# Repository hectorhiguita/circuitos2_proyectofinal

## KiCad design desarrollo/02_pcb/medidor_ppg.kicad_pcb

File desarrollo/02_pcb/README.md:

# PCB — Medidor PPG (KiCad 10)

Placa 80 × 52 mm, 2 capas, todo THT. Plano GND en las dos caras. DRC: 0 errores, 0 pendientes, esquema = placa.

## Archivos
| Archivo | Qué es |
|---|---|
| `medidor_ppg.kicad_pro` | Abrir en KiCad |
| `fab/medidor_ppg_gerbers_JLCPCB.zip` | Subir a JLCPCB tal cual |
| `fab/medidor_ppg_BOM.csv` | Lista de piezas de la placa |
| `fab/medidor_ppg_esquema.pdf` | Esquema para el informe |
| `fab/medidor_ppg_montaje_superior.pdf` | Guía de montaje (cara superior) |
| `img/*.png` | Vistas 3D |
| `componentes.py` | Netlist (fuente única) |
| `generar_esquema.py`, `generar_pcb.py`, `fabricar.sh` | Regeneran todo |

Regenerar: `python3 generar_esquema.py && python3 generar_pcb.py && ./fabricar.sh`.
**Riesgo:** `generar_pcb.py` sobrescribe la placa. Si la editas a mano en KiCad, no lo vuelvas a correr.

## Esquema legible por bloques
El esquema `medidor_ppg.kicad_sch` está dibujado **por etapas** (cada una en su recuadro), con la señal fluyendo de izquierda a derecha: sensor → acople → buffer → preamp → Sallen-Key → salida → protección → ADC. Lo genera `construir_esquema.py` (usa `esq_bloques_lib.py`), leyendo el mismo `componentes.py`, así que el **netlist es idéntico** al generador antiguo: la PCB, el ERC y la simulación no cambian.

- Regenerar el esquema legible: `python3 construir_esquema.py`
- Vista previa: `img/esquema_bloques.png`
- El generador antiguo por etiquetas quedó como respaldo en `generar_esquema_etiquetas.py.bak` y el esquema anterior en `medidor_ppg.kicad_sch.bak_etiquetas`.

## Opción sin PCB: baquela perforada 9 × 7 cm
Todas las huellas usan paso de 2.54 mm. Por eso la misma ubicación sirve en baquela universal (35 × 27 agujeros). Ocupa 32 × 19 agujeros.

| Archivo | Uso |
|---|---|
| `perforada/vista_componentes.pdf` | Imprimir al **100 %**, pegar sobre la baquela y pinchar las piezas |
| `perforada/vista_soldadura.pdf` | Vista desde abajo (espejada). Cada línea = un cable |
| `perforada/conexiones.md` | 99 conexiones con casilla para marcar. Ej.: `R15.1 (R5) → C12.1 (P19)` |

Columnas = letras, filas = números (como un tablero de ajedrez). Usa cable de wire-wrap o hilos de UTP. GND, +5V y +3V3 con cable más grueso.
Regenerar: `python3 perforada.py`.

## Pedido en JLCPCB
2 capas, 80×52 mm, 1.6 mm, HASL, cualquier color. 5 placas cuestan ~2 USD más el envío.

## Antes de soldar: verifica con el calibrador
1. **SuperMini:** filas a **15.24 mm**. Pon la placa sobre la serigrafía. El pin `5V` debe quedar del lado del USB, en la fila de arriba.
   Si los pines quedan al revés, se puede montar el SuperMini boca abajo: así se cruzan las filas y el orden se mantiene.
2. **Buzzer:** la pata `+` va en el pad cuadrado.

## Orden de soldadura (de bajo a alto)
1. Resistencias (paradas) y diodos. `K` en la serigrafía = cátodo (raya).
2. Zócalo DIP-14 (muesca hacia arriba en la serigrafía). El LM324 va al final.
3. Condensadores cerámicos, puntos de prueba TP1–TP7.
4. Transistor 2N3904 (cara plana como la serigrafía), trimmer RV1.
5. Condensadores de film, electrolíticos (pata larga `+`), conectores, zócalos del SuperMini y buzzer.

## Conector de energía J5 (cables al piso de la caja)
| Pin | Va a |
|---|---|
| 1 B+ | TP4056 OUT+ |
| 2 SWa | Interruptor, pata 1 |
| 3 SWb | Interruptor, pata común |
| 4 MT+ | MT3608 IN+ |
| 5 B− | TP4056 OUT− |
| 6 MT− | MT3608 IN− |
| 7 5V | MT3608 OUT+ |
| 8 G | MT3608 OUT− |

La batería va a B+ / B− del **TP4056**, no a la placa.

## Sensor J1 (JST-XH 4, hacia la pinza)
| Pin | Va a |
|---|---|
| 1 LED+ | Ánodo del LED IR (pata larga) |
| 2 LED− | Cátodo del LED IR |
| 3 PD-K | Cátodo del fotodiodo (pata corta / lado plano) |
| 4 PD-A | Ánodo del fotodiodo |

Usa cable apantallado o trenzado. La malla va a GND.

## Prueba por etapas (lo pide la guía)
1. **Sin LM324 ni SuperMini:** conecta la LiPo y ajusta el MT3608 a **5.00 V** en el pin 7 de J5.
2. Pon el SuperMini sin el LM324. Mide **3.3 V** en el pin 3V3 y **1.32 V** en TP6.
3. Pon el LM324, con el dedo en la pinza. Mira cada punto con el osciloscopio:

| TP | Etapa | Esperado |
|---|---|---|
| TP1 | Sensor | DC 0.1–1 V, pulso de pocos mV |
| TP2 | Buffer | ≈1.32 V con el pulso encima |
| TP3 | Preamp ×34 | ≈1.32 V, pulso ≈0.1 Vpp |
| TP4 | Sallen-Key | Igual, más suave |
| TP5 | **Punto 6** | 1.32 V ± 0.5 V. Nunca < 0 V ni > 2.5 V |
| TP7 | GND | Tierra del osciloscopio |

4. Ajusta RV1 hasta ver **0.8–1.6 Vpp** en TP5.

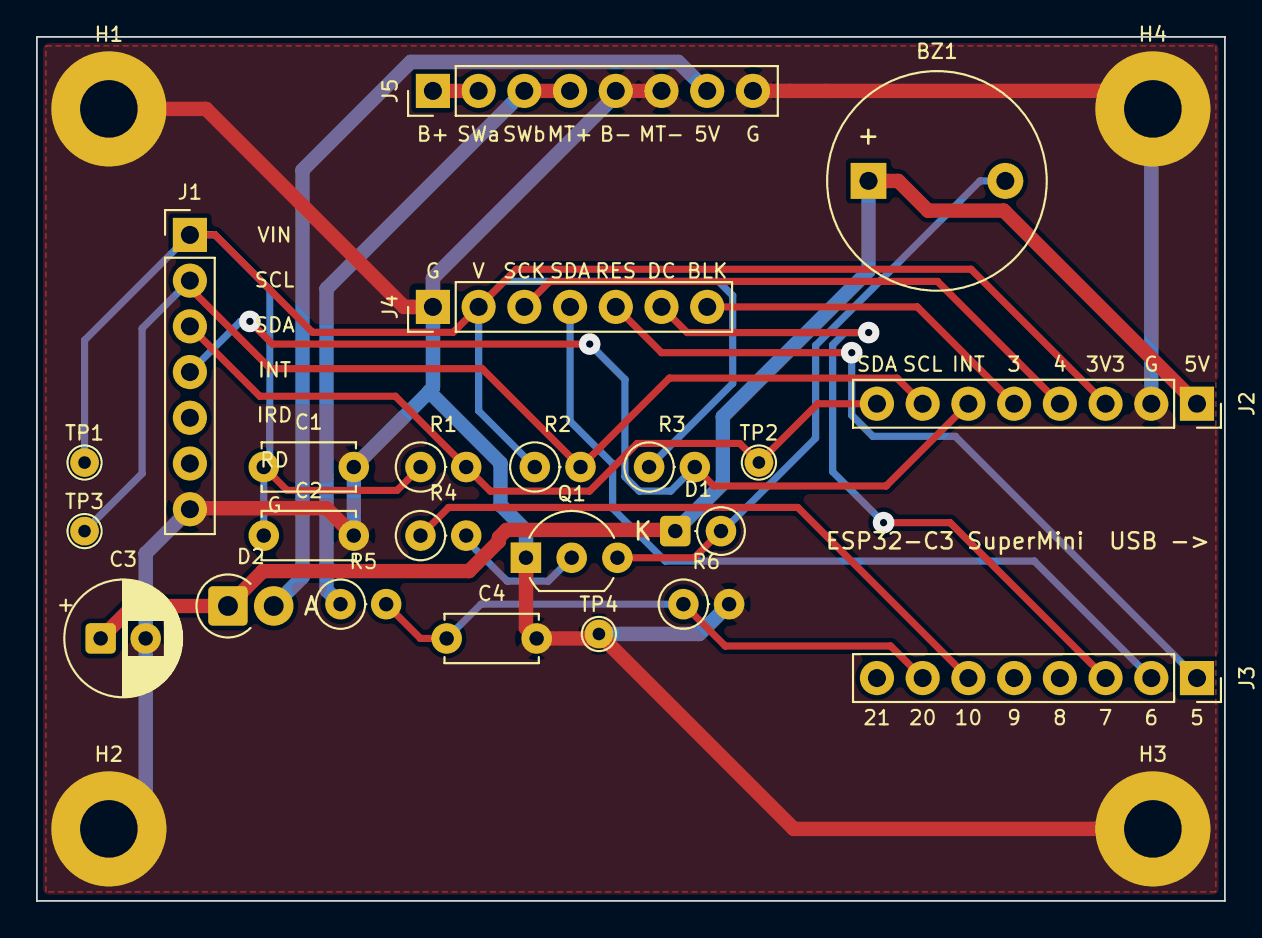
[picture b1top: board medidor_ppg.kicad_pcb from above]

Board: 2 copper layers, 66.0 x 48.0 mm, 27 parts (0 on the bottom side), 18 nets.

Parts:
BZ1: Buzzer 5V; Buzzer_12x9.5RM7.6
C1, C2, C4: 100nF; C_Disc_D5.0mm_W2.5mm_P5.00mm
C3: 100uF; CP_Radial_D6.3mm_P2.50mm
D1: 1N4148; D_DO-35_SOD27_P2.54mm_Vertical_CathodeUp
D2: 1N5819; D_DO-41_SOD81_P2.54mm_Vertical_AnodeUp
H1, H2, H3, H4: M3; MountingHole_3.2mm_M3_Pad
J1: MAX30102; PinHeader_1x07_P2.54mm_Vertical
J2: C3_5V-IO0; PinSocket_1x08_P2.54mm_Vertical
J3: C3_IO5-IO21; PinSocket_1x08_P2.54mm_Vertical
J4: TFT 1.3 ST7789; PinHeader_1x07_P2.54mm_Vertical
J5: ENERGIA; PinHeader_1x08_P2.54mm_Vertical
Q1: 2N3904; TO-92_Inline_Wide
R1, R2, R3: 4.7k; R_Axial_DIN0207_L6.3mm_D2.5mm_P2.54mm_Vertical
R4: 1k; R_Axial_DIN0207_L6.3mm_D2.5mm_P2.54mm_Vertical
R5, R6: 100k; R_Axial_DIN0207_L6.3mm_D2.5mm_P2.54mm_Vertical
TP1: +3V3; TestPoint_THTPad_D1.5mm_Drill0.7mm
TP2: SDA; TestPoint_THTPad_D1.5mm_Drill0.7mm
TP3: SCL; TestPoint_THTPad_D1.5mm_Drill0.7mm
TP4: GND; TestPoint_THTPad_D1.5mm_Drill0.7mm

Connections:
+3V3: C1.1, C2.1, J1.1, J2.3, J4.2, R1.1, R2.1, R3.1, TP1.1
+5V: BZ1.1, C3.1, D1.1, D2.1, J2.1
/+5V_B: D2.2, J5.7
/BAT: J5.1, J5.2
/BUZ: J3.6, R4.1
/BZK: BZ1.2, D1.2, Q1.3
/INT: J1.4, J2.6, R3.2
/QB: Q1.2, R4.2
/SCL: J1.2, J2.7, R2.2, TP3.1
/SDA: J1.3, J2.8, R1.2, TP2.1
/TFT_BLK: J2.5, J4.7
/TFT_DC: J3.3, J4.6
/TFT_RES: J3.1, J4.5
/TFT_SCK: J2.4, J4.3
/TFT_SDA: J3.2, J4.4
/VBAT_S: C4.1, J3.7, R5.2, R6.1
/VSW: J5.3, J5.4, R5.1
GND: C1.2, C2.2, C3.2, C4.2, H1.1, H2.1, H3.1, H4.1, J1.7, J2.2, J4.1, J5.5, J5.6, J5.8, Q1.1, R6.2, TP4.1

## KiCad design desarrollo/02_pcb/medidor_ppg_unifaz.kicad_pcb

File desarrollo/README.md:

# Medidor de ritmo cardiaco PPG — Proyecto final Circuitos Eléctricos II (ITM)

LED IR + fotodiodo → LM324 (6 etapas) → ESP32-C3 SuperMini → OLED + buzzer → MQTT → tablero + alertas por correo y WhatsApp.

| Carpeta | Contenido | Estado |
|---|---|---|
| `SPEC.md` | Especificación: pines, valores, contrato MQTT | ✅ |
| `01_analogico/` | Netlist ngspice, simulación, gráficas | ✅ simulado |
| `02_pcb/` | KiCad 10: esquema, PCB, Gerbers JLCPCB, BOM | ✅ DRC 0 errores |
| `03_firmware/` | PlatformIO (ESP32-C3) | ✅ compila, 13 pruebas OK |
| `04_iot/` | Mosquitto + Node-RED (tablero, alertas) + simulador | ✅ probado con simulador |
| `05_carcasa/` | OpenSCAD + STL | ✅ STL listos |
| `06_informe/` | Informe escrito | ✅ borrador (faltan fotos y medidas reales) |

## Lista de compras
| # | Pieza | Cant | Nota |
|---|---|---|---|
| 1 | ESP32-C3 SuperMini | 1 | USB-C |
| 2 | OLED 0.96" I2C SSD1306 (4 pines) | 1 | dirección 0x3C |
| 3 | LM324N (DIP-14) + zócalo DIP-14 | 1 | |
| 4 | LED IR 940 nm 5 mm | 1 | |
| 5 | Fotodiodo IR 5 mm (o BPW34) | 1 | **no** fototransistor |
| 6 | Batería LiPo BL-3.7V-1000-25C (68×34×6 mm) | 1 | cortar el conector rojo y soldar al TP4056 |
| 7 | Módulo TP4056 USB-C con protección (DW01) | 1 | |
| 8 | Módulo elevador MT3608 | 1 | ajustar a 5.0 V |
| 9 | Interruptor deslizante SS12D00 | 1 | |
| 10 | Buzzer activo 5 V, 12 mm | 1 | |
| 11 | Trimmer multivuelta 3296W 200 kΩ | 1 | |
| 12 | Condensador film (MKT) 1 µF 63 V | 3 | paso 5 mm |
| 13 | Condensador film 470 nF 63 V | 1 | paso 5 mm |
| 14 | Electrolítico 100 µF 16 V (6.3 mm) | 3 | |
| 15 | Cerámico 100 nF | 6 | |
| 16 | Cerámico 47 nF | 1 | |
| 17 | Cerámico 10 nF | 1 | |
| 18 | Resistencias 1/4 W: 220, 1k ×3, 1.5k ×2, 4.7k, 10k ×3, 47k ×3, 100k ×2, 330k, 470k ×2 | 19 | |
| 19 | Diodo BAT85 | 2 | Schottky |
| 20 | Diodo 1N5819 | 1 | |
| 21 | Diodo 1N4148 | 1 | |
| 22 | Transistor 2N3904 | 1 | |
| 23 | Conector JST-XH 4 pines (macho PCB + hembra con cable) | 1 | sensor |
| 24 | Regleta hembra 1×8 (2.54) | 2 | zócalo SuperMini |
| 25 | Regleta macho 1×8 y 1×4 | 1+1 | J5, J4 |
| 26 | Tornillos M3 + insertos, M2, liga | — | ver `05_carcasa/README.md` |
| 27 | PCB JLCPCB 80×52 mm | 5 | `02_pcb/fab/medidor_ppg_gerbers_JLCPCB.zip` |

## Orden sugerido
1. Pedir la PCB e imprimir la carcasa (tardan más).
2. Probar firmware y tablero **sin** hardware: `03_firmware` entorno `c3_demo` + `04_iot` con simulador.
3. Soldar y validar por etapas con el osciloscopio (`02_pcb/README.md`).
4. Ajustar RV1. Probar alertas. Tomar fotos y capturas para el informe.

## Riesgos
- **Punto 6** nunca debe pasar de 2.5 V ni bajar de 0 V. Mídelo antes de poner el SuperMini.
- Ajusta el **MT3608 a 5.0 V** antes de conectar la placa.
- La LiPo debe tener protección. No la cargues sin vigilar.
- El `.env` de `04_iot` tiene claves. No lo subas a internet.

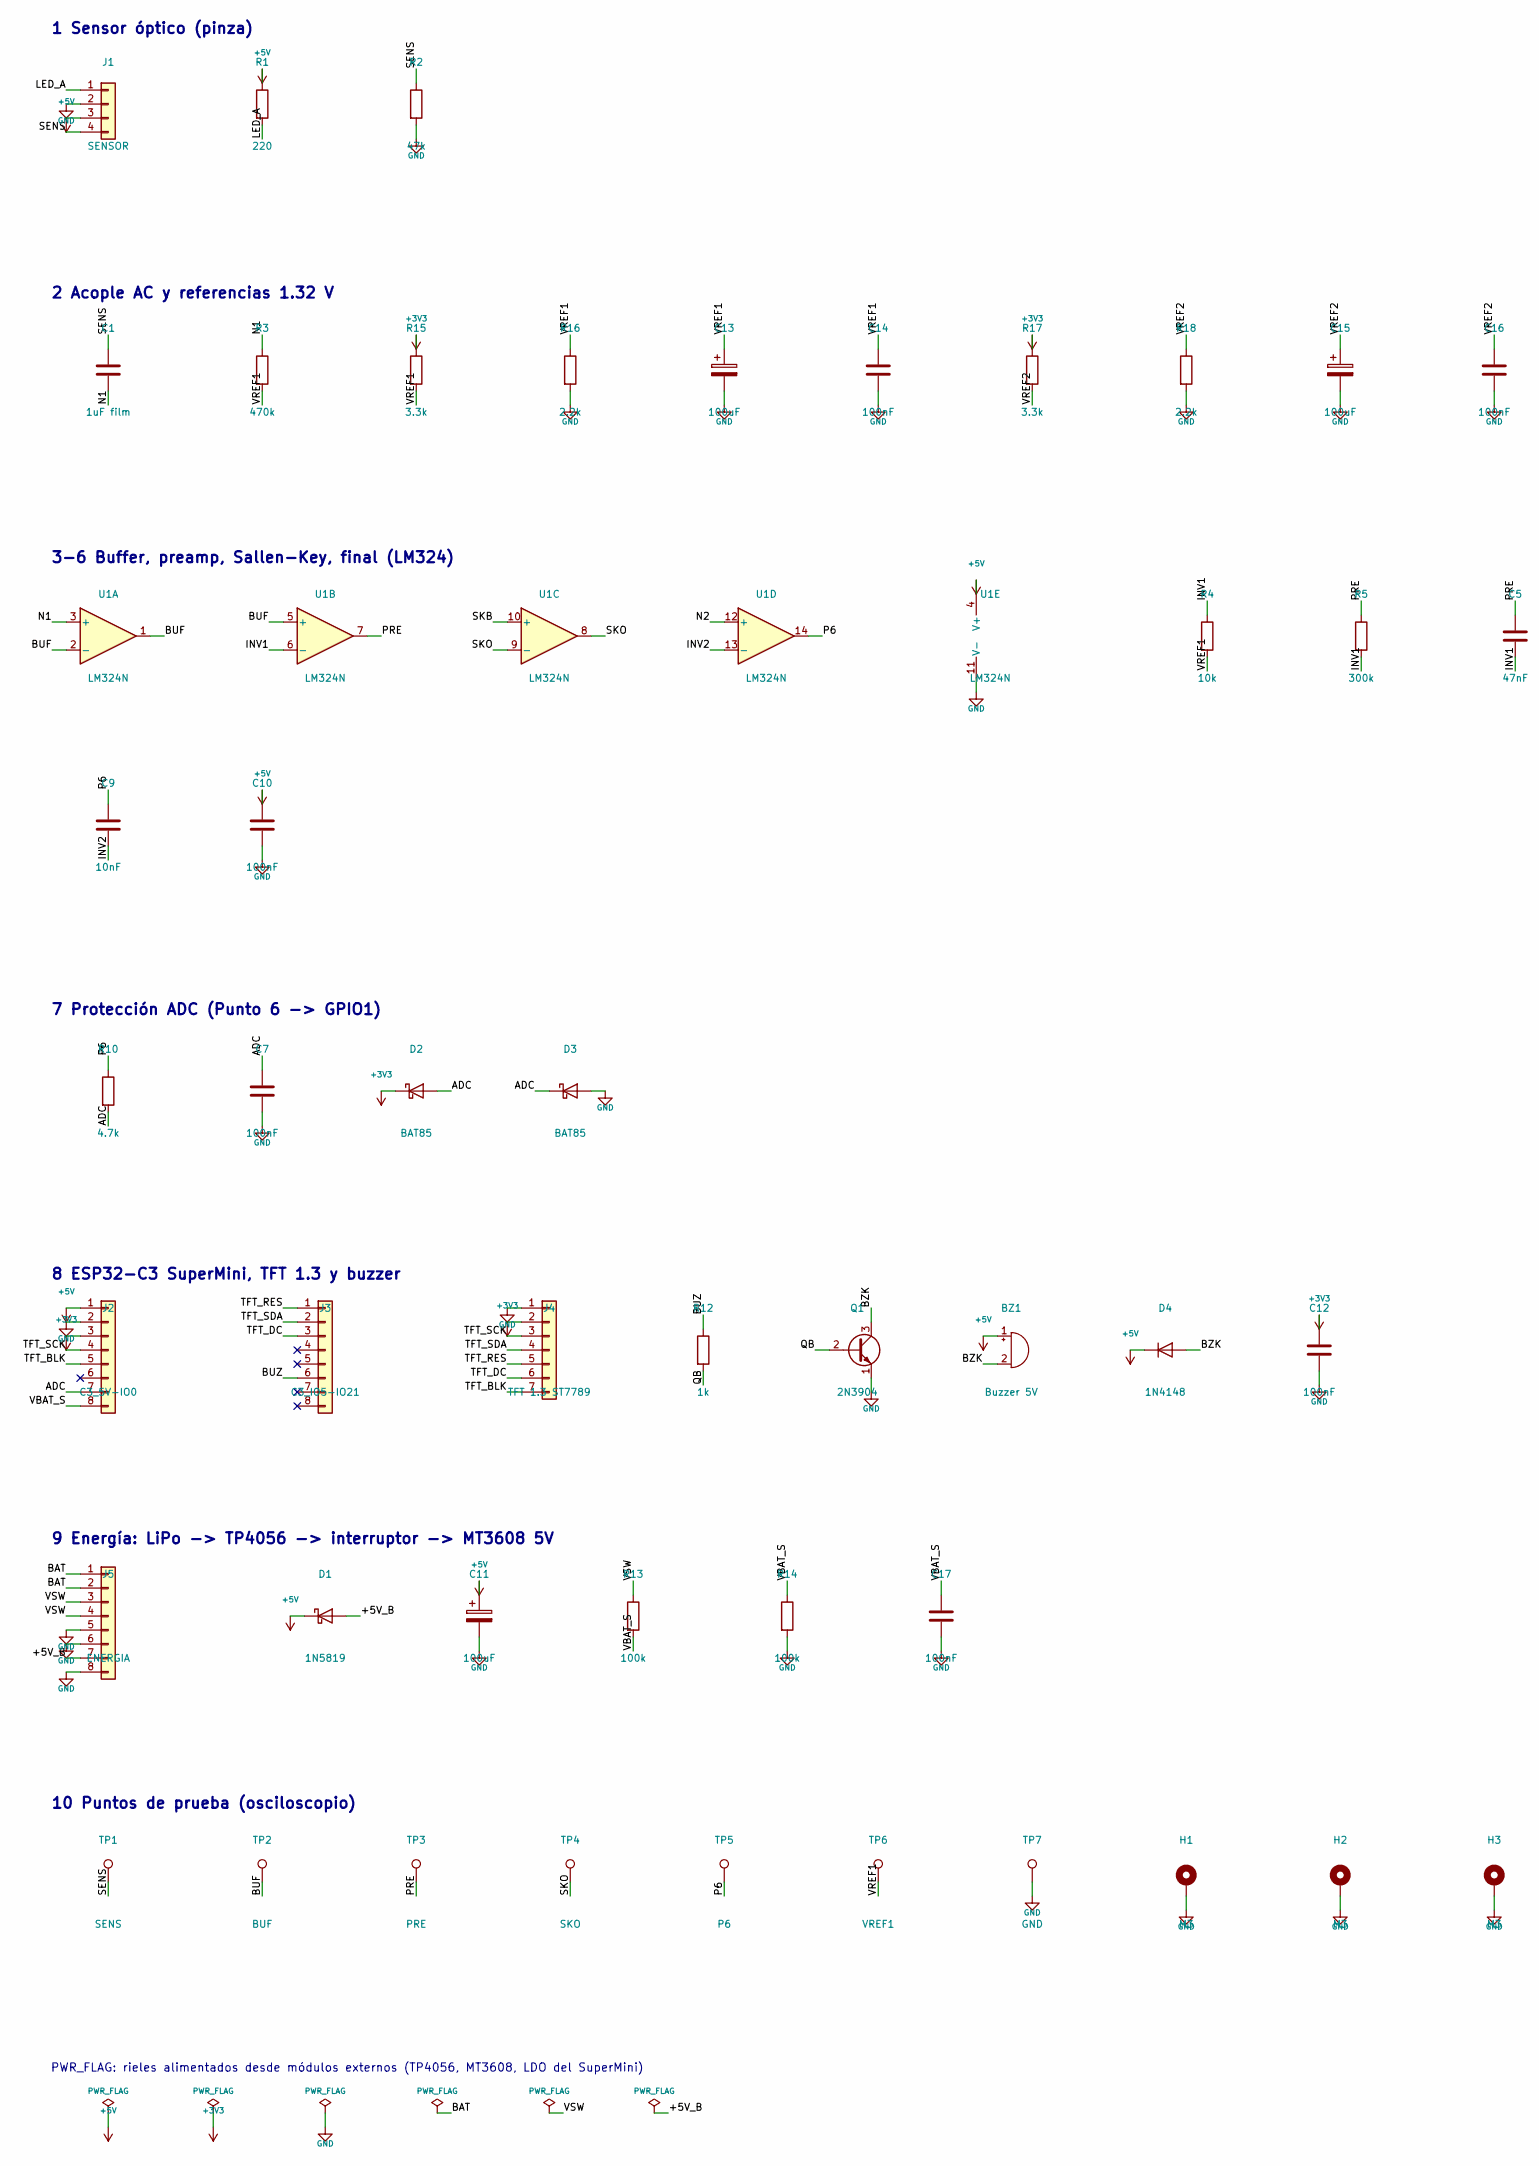
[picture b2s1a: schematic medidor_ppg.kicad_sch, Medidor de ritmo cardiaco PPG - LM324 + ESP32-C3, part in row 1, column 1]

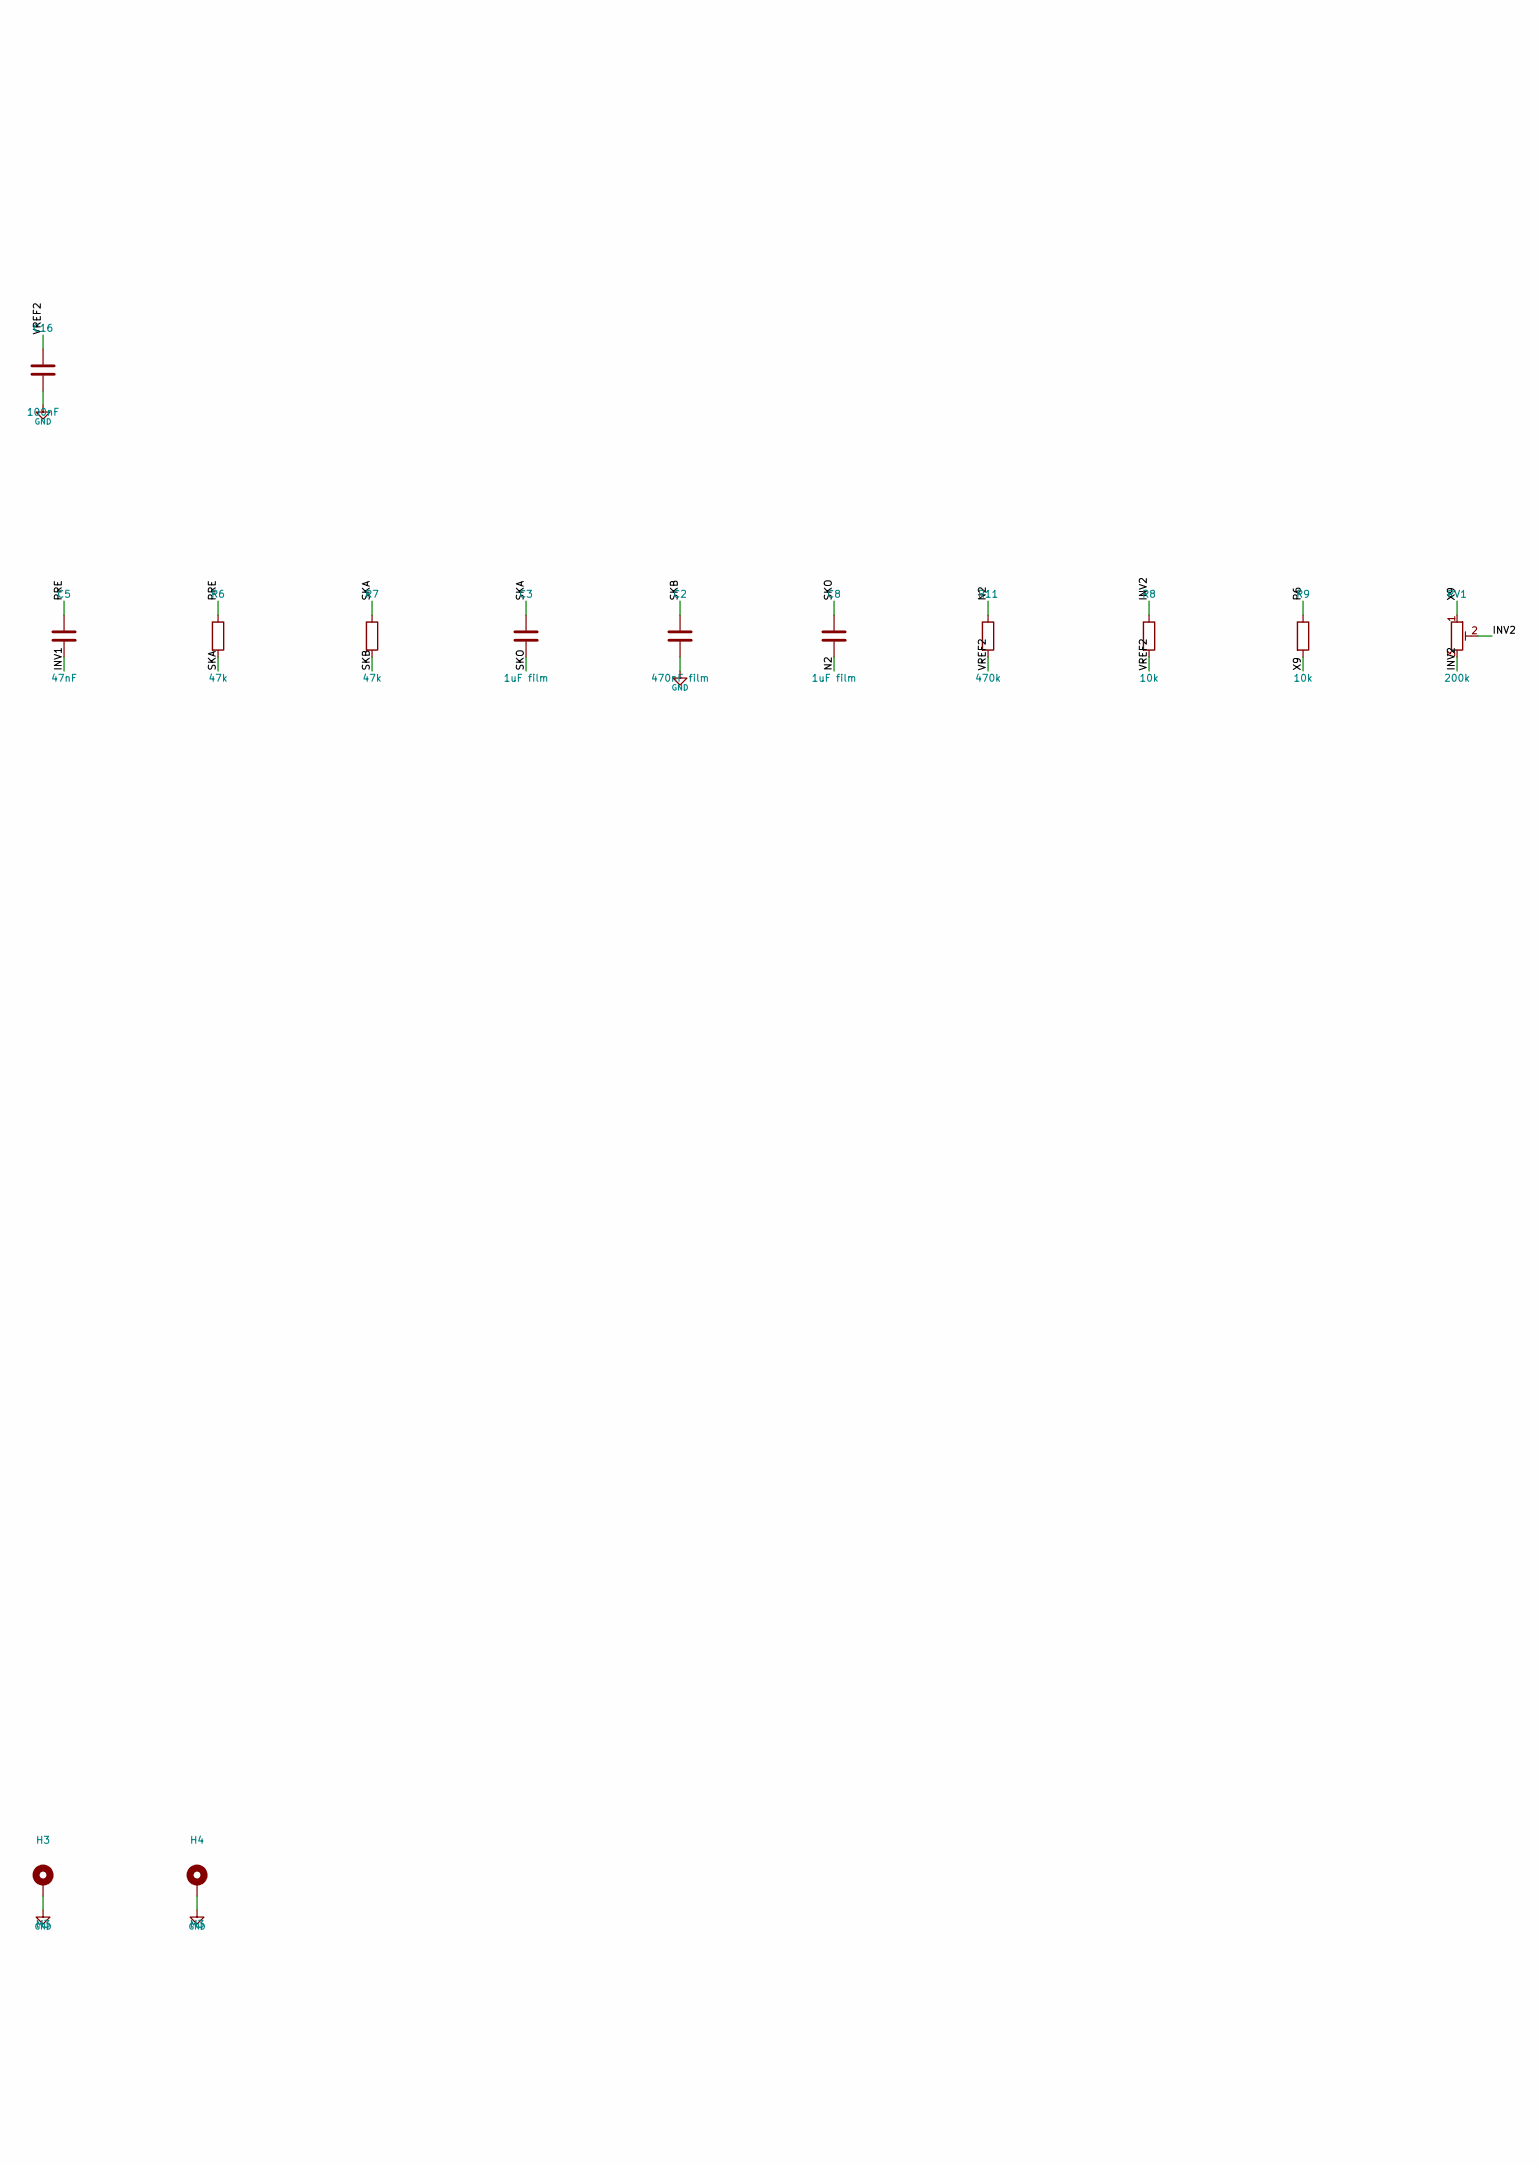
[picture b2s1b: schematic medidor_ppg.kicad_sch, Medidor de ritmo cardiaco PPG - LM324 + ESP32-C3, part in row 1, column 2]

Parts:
BZ1: Buzzer 5V; Buzzer_12x9.5RM7.6
C1, C3, C8: 1uF film; C_Rect_L7.2mm_W5.5mm_P5.00mm_FKS2_FKP2_MKS2_MKP2
C2: 470nF film; C_Rect_L7.2mm_W5.5mm_P5.00mm_FKS2_FKP2_MKS2_MKP2
C5: 47nF; C_Disc_D5.0mm_W2.5mm_P5.00mm
C7, C10, C12, C14, C16, C17: 100nF; C_Disc_D5.0mm_W2.5mm_P5.00mm
C9: 10nF; C_Disc_D5.0mm_W2.5mm_P5.00mm
C11, C13, C15: 100uF; CP_Radial_D6.3mm_P2.50mm
D1: 1N5819; D_DO-41_SOD81_P2.54mm_Vertical_AnodeUp
D2, D3: BAT85; D_DO-35_SOD27_P2.54mm_Vertical_CathodeUp
D4: 1N4148; D_DO-35_SOD27_P2.54mm_Vertical_CathodeUp
H1, H2, H3, H4: M3; MountingHole_3.2mm_M3_Pad
J1: SENSOR; JST_XH_B4B-XH-A_1x04_P2.50mm_Vertical
J2: C3_5V-IO0; PinSocket_1x08_P2.54mm_Vertical
J3: C3_IO5-IO21; PinSocket_1x08_P2.54mm_Vertical
J4: TFT 1.3 ST7789; PinHeader_1x07_P2.54mm_Vertical
J5: ENERGIA; PinHeader_1x08_P2.54mm_Vertical
Q1: 2N3904; TO-92_Inline_Wide
R1: 220; R_Axial_DIN0207_L6.3mm_D2.5mm_P2.54mm_Vertical
R2, R6, R7: 47k; R_Axial_DIN0207_L6.3mm_D2.5mm_P2.54mm_Vertical
R3, R11: 470k; R_Axial_DIN0207_L6.3mm_D2.5mm_P2.54mm_Vertical
R4, R8, R9: 10k; R_Axial_DIN0207_L6.3mm_D2.5mm_P2.54mm_Vertical
R5: 300k; R_Axial_DIN0207_L6.3mm_D2.5mm_P2.54mm_Vertical
R10: 4.7k; R_Axial_DIN0207_L6.3mm_D2.5mm_P2.54mm_Vertical
R12: 1k; R_Axial_DIN0207_L6.3mm_D2.5mm_P2.54mm_Vertical
R13, R14: 100k; R_Axial_DIN0207_L6.3mm_D2.5mm_P2.54mm_Vertical
R15, R17: 3.3k; R_Axial_DIN0207_L6.3mm_D2.5mm_P2.54mm_Vertical
R16, R18: 2.2k; R_Axial_DIN0207_L6.3mm_D2.5mm_P2.54mm_Vertical
RV1: 200k; Potentiometer_Bourns_3296W_Vertical
TP1: SENS; TestPoint_THTPad_D1.5mm_Drill0.7mm
TP2: BUF; TestPoint_THTPad_D1.5mm_Drill0.7mm
TP3: PRE; TestPoint_THTPad_D1.5mm_Drill0.7mm
TP4: SKO; TestPoint_THTPad_D1.5mm_Drill0.7mm
TP5: P6; TestPoint_THTPad_D1.5mm_Drill0.7mm
TP6: VREF1; TestPoint_THTPad_D1.5mm_Drill0.7mm
TP7: GND; TestPoint_THTPad_D1.5mm_Drill0.7mm
U1: LM324N; DIP-14_W7.62mm_Socket

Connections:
+3V3: C12.1, D2.1 (K), J2.3, J4.2, R15.1, R17.1
+5V: BZ1.1 (+), C10.1, C11.1, D1.1 (K), D4.1 (K), J1.3, J2.1, R1.1, U1.4 (V+)
/+5V_B: D1.2 (A), J5.7
/ADC: C7.1, D2.2 (A), D3.1 (K), J2.7, R10.2
/BAT: J5.1, J5.2
/BUF: TP2.1, U1.1, U1.2 (-), U1.5 (+)
/BUZ: J3.6, R12.1
/BZK: BZ1.2 (-), D4.2 (A), Q1.3 (C)
/INV1: C5.2, R4.1, R5.2, U1.6 (-)
/INV2: C9.2, R8.1, RV1.2, RV1.3, U1.13 (-)
/LED_A: J1.1, R1.2
/N1: C1.2, R3.1, U1.3 (+)
/N2: C8.2, R11.1, U1.12 (+)
/P6: C9.1, R9.1, R10.1, TP5.1, U1.14
/PRE: C5.1, R5.1, R6.1, TP3.1, U1.7
/QB: Q1.2 (B), R12.2
/SENS: C1.1, J1.4, R2.1, TP1.1
/SKA: C3.1, R6.2, R7.1
/SKB: C2.1, R7.2, U1.10 (+)
/SKO: C3.2, C8.1, TP4.1, U1.8, U1.9 (-)
/TFT_BLK: J2.5, J4.7
/TFT_DC: J3.3, J4.6
/TFT_RES: J3.1, J4.5
/TFT_SCK: J2.4, J4.3
/TFT_SDA: J3.2, J4.4
/VBAT_S: C17.1, J2.8, R13.2, R14.1
/VREF1: C13.1, C14.1, R3.2, R4.2, R15.2, R16.1, TP6.1
/VREF2: C15.1, C16.1, R8.2, R11.2, R17.2, R18.1
/VSW: J5.3, J5.4, R13.1
/X9: R9.2, RV1.1
GND: C2.2, C7.2, C10.2, C11.2, C12.2, C13.2, C14.2, C15.2, C16.2, C17.2, D3.2 (A), H1.1, H2.1, H3.1, H4.1, J1.2, J2.2, J4.1, J5.5, J5.6, J5.8, Q1.1 (E), R2.2, R14.2, R16.2, R18.2, TP7.1, U1.11 (V-)

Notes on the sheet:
1 Sensor óptico (pinza)
2 Acople AC y referencias 1.32 V
3-6 Buffer, preamp, Sallen-Key, final (LM324)
7 Protección ADC (Punto 6 -> GPIO1)
8 ESP32-C3 SuperMini, TFT 1.3 y buzzer
9 Energía: LiPo -> TP4056 -> interruptor -> MT3608 5V
10 Puntos de prueba (osciloscopio)
PWR_FLAG: rieles alimentados desde módulos externos (TP4056, MT3608, LDO del SuperMini)

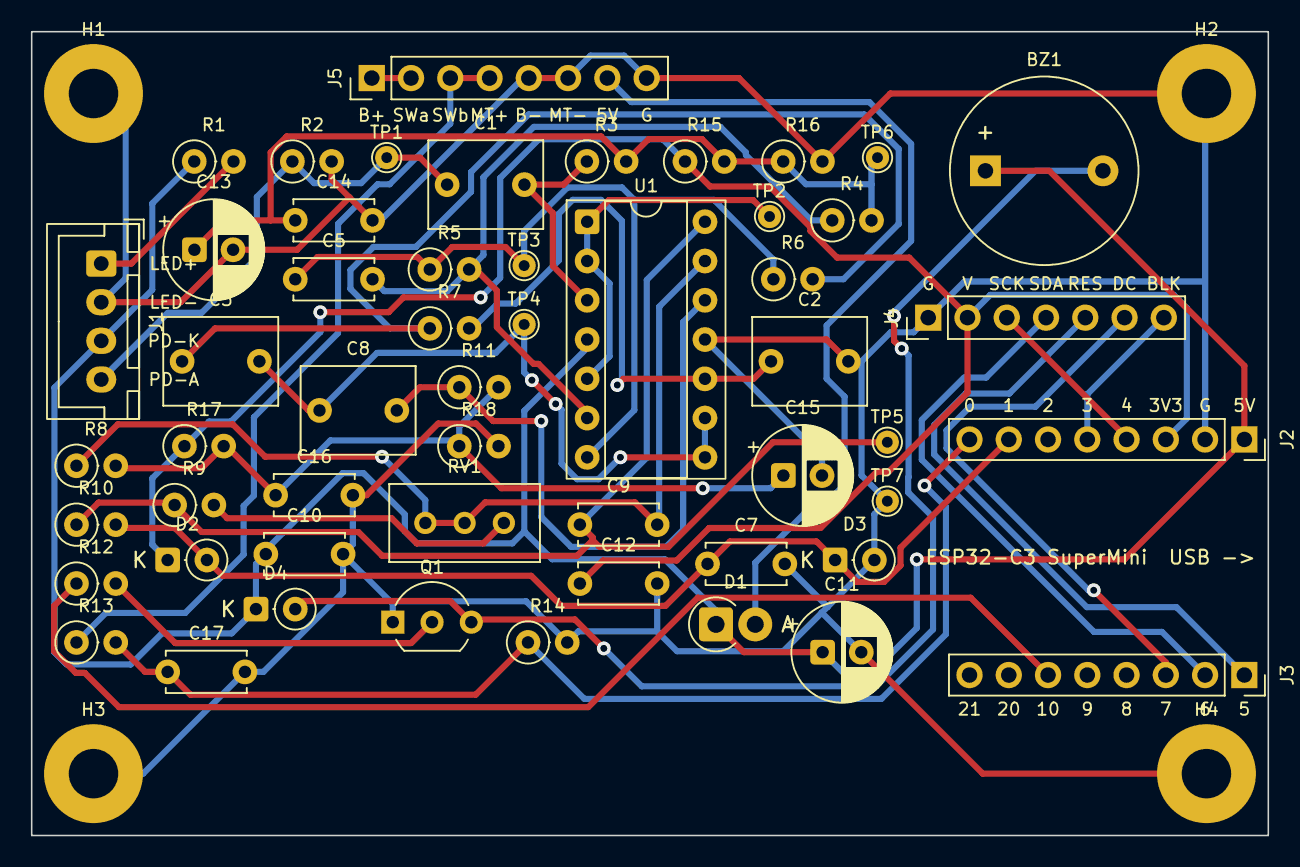
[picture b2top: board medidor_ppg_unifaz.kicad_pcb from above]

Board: 2 copper layers, 80.0 x 52.0 mm, 57 parts (0 on the bottom side), 31 nets.

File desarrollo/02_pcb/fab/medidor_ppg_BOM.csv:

"Ref","Valor","Huella","Cant"
"BZ1","Buzzer 5V","Buzzer_Beeper:Buzzer_12x9.5RM7.6","1"
"C1,C3,C8","1uF film","Capacitor_THT:C_Rect_L7.2mm_W5.5mm_P5.00mm_FKS2_FKP2_MKS2_MKP2","3"
"C2","470nF film","Capacitor_THT:C_Rect_L7.2mm_W5.5mm_P5.00mm_FKS2_FKP2_MKS2_MKP2","1"
"C5","47nF","Capacitor_THT:C_Disc_D5.0mm_W2.5mm_P5.00mm","1"
"C7,C10,C12,C14,C16,C17","100nF","Capacitor_THT:C_Disc_D5.0mm_W2.5mm_P5.00mm","6"
"C9","10nF","Capacitor_THT:C_Disc_D5.0mm_W2.5mm_P5.00mm","1"
"C11,C13,C15","100uF","Capacitor_THT:CP_Radial_D6.3mm_P2.50mm","3"
"D1","1N5819","Diode_THT:D_DO-41_SOD81_P2.54mm_Vertical_AnodeUp","1"
"D2,D3","BAT85","Diode_THT:D_DO-35_SOD27_P2.54mm_Vertical_CathodeUp","2"
"D4","1N4148","Diode_THT:D_DO-35_SOD27_P2.54mm_Vertical_CathodeUp","1"
"J1","SENSOR","Connector_JST:JST_XH_B4B-XH-A_1x04_P2.50mm_Vertical","1"
"J2","C3_5V-IO0","Connector_PinSocket_2.54mm:PinSocket_1x08_P2.54mm_Vertical","1"
"J3","C3_IO5-IO21","Connector_PinSocket_2.54mm:PinSocket_1x08_P2.54mm_Vertical","1"
"J4","TFT 1.3 ST7789","Connector_PinHeader_2.54mm:PinHeader_1x07_P2.54mm_Vertical","1"
"J5","ENERGIA","Connector_PinHeader_2.54mm:PinHeader_1x08_P2.54mm_Vertical","1"
"Q1","2N3904","Package_TO_SOT_THT:TO-92_Inline_Wide","1"
"R1","220","Resistor_THT:R_Axial_DIN0207_L6.3mm_D2.5mm_P2.54mm_Vertical","1"
"R2,R6,R7","47k","Resistor_THT:R_Axial_DIN0207_L6.3mm_D2.5mm_P2.54mm_Vertical","3"
"R3,R11","470k","Resistor_THT:R_Axial_DIN0207_L6.3mm_D2.5mm_P2.54mm_Vertical","2"
"R4,R8,R9","10k","Resistor_THT:R_Axial_DIN0207_L6.3mm_D2.5mm_P2.54mm_Vertical","3"
"R5","300k","Resistor_THT:R_Axial_DIN0207_L6.3mm_D2.5mm_P2.54mm_Vertical","1"
"R10","4.7k","Resistor_THT:R_Axial_DIN0207_L6.3mm_D2.5mm_P2.54mm_Vertical","1"
"R12","1k","Resistor_THT:R_Axial_DIN0207_L6.3mm_D2.5mm_P2.54mm_Vertical","1"
"R13,R14","100k","Resistor_THT:R_Axial_DIN0207_L6.3mm_D2.5mm_P2.54mm_Vertical","2"
"R15,R17","3.3k","Resistor_THT:R_Axial_DIN0207_L6.3mm_D2.5mm_P2.54mm_Vertical","2"
"R16,R18","2.2k","Resistor_THT:R_Axial_DIN0207_L6.3mm_D2.5mm_P2.54mm_Vertical","2"
"RV1","200k","Potentiometer_THT:Potentiometer_Bourns_3296W_Vertical","1"
"U1","LM324N","Package_DIP:DIP-14_W7.62mm_Socket","1"

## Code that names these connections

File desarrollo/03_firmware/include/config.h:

// config.h - Pines y constantes del firmware (ver ../SPEC.md).
#pragma once

#if __has_include("secrets.h")
#include "secrets.h"
#else
#warning "include/secrets.h no existe: usando secrets.example.h (copie y edite el archivo)"
#include "secrets.example.h"
#endif

#define FW_VERSION "1.0.0"

// -DDEMO_SENSOR=1 (entorno c3_demo): señal PPG sintética, sin tarjeta analógica.
#ifndef DEMO_SENSOR
#define DEMO_SENSOR 0
#endif

// ------------------------------------------------------------ pines ESP32-C3 SuperMini
#define PIN_PPG      1   // ADC1_CH1, punto 6 (señal acondicionada)
#define PIN_BAT      0   // ADC1_CH0, divisor 100k/100k (Vbat/2)
#define PIN_SDA      6   // solo OLED (c3_oled)
#define PIN_SCL      7
#define PIN_BUZZER   10  // base del 2N3904 vía 1k, activo en alto
#define PIN_BOTON    9   // BOOT, activo en bajo
#define PIN_LED      8   // LED azul de la placa, activo en bajo

// Pantalla: TFT 1.3" ST7789 240x240 SPI (por defecto) u OLED 0.96" SSD1306 I2C (-DPANTALLA_TFT=0)
#ifndef PANTALLA_TFT
#define PANTALLA_TFT 1
#endif
#define TFT_SCK      4
#define TFT_MOSI     6   // "SDA" en la serigrafía del módulo
#define TFT_DC       7
#define TFT_RST      5
#define TFT_BLK      3   // luz de fondo (PWM)
#define TFT_BRILLO   200 // 0..255
#define TFT_ROTACION 0   // 0..3 según cómo quede montada
#define TFT_PERIODO_MS 80

#define OLED_ADDR    0x3C
#define OLED_W       128
#define OLED_H       64

// ------------------------------------------------------------ muestreo
#define FS_HZ             200   // frecuencia de muestreo
#define ADC_PROMEDIO      8     // lecturas promediadas por muestra
#define BAT_DIVISOR       2.0f  // 100k/100k
#define BAT_V_BAJA        3.40f // LiPo 1S: aviso de batería baja
#define DECIMACION_ONDA   4     // 200 Hz / 4 = 50 Hz (MQTT "onda" y pantalla)

// Polaridad: en transmisión la sístole BAJA la tensión del fotodiodo -> invertir.
#ifndef INVERTIR_SENAL
#define INVERTIR_SENAL    1
#endif

// ------------------------------------------------------------ indicadores
#define BEEP_MS           30
#define LED_MS            60
#define BOTON_LARGO_MS    800

// ------------------------------------------------------------ alertas / config por defecto
#define BPM_MIN_DEF       50
#define BPM_MAX_DEF       120
#define BUZZER_DEF        true

// ------------------------------------------------------------ red
#define MQTT_PREFIJO      "pulso/"
#define WIFI_REINTENTO_MS 15000
#define MQTT_REINTENTO_MS 5000

// ------------------------------------------------------------ batería LiPo 1S (TP4056)
// Curva de descarga típica LiPo a carga baja: 4.20 V = 100 %, 3.30 V = 0 %.
static inline int bateria_pct(float v) {
  static const float tv[] = {3.30f, 3.50f, 3.60f, 3.70f, 3.75f, 3.80f, 3.85f, 3.95f, 4.05f, 4.20f};
  static const int   tp[] = {0,     5,     10,    20,    30,    40,    50,    70,    85,    100};
  const int n = sizeof(tv) / sizeof(tv[0]);
  if (v <= tv[0]) return 0;
  if (v >= tv[n - 1]) return 100;
  for (int i = 1; i < n; i++) {
    if (v < tv[i]) return tp[i - 1] + (int)((v - tv[i - 1]) / (tv[i] - tv[i - 1]) * (tp[i] - tp[i - 1]) + 0.5f);
  }
  return 100;
}

// ------------------------------------------------------------ depuración serie
// 0 = registro legible 1 Hz, 1 = CSV para el graficador serie (tecla 'p' alterna)
#ifndef SERIAL_PLOT_DEF
#define SERIAL_PLOT_DEF   0
#endif
